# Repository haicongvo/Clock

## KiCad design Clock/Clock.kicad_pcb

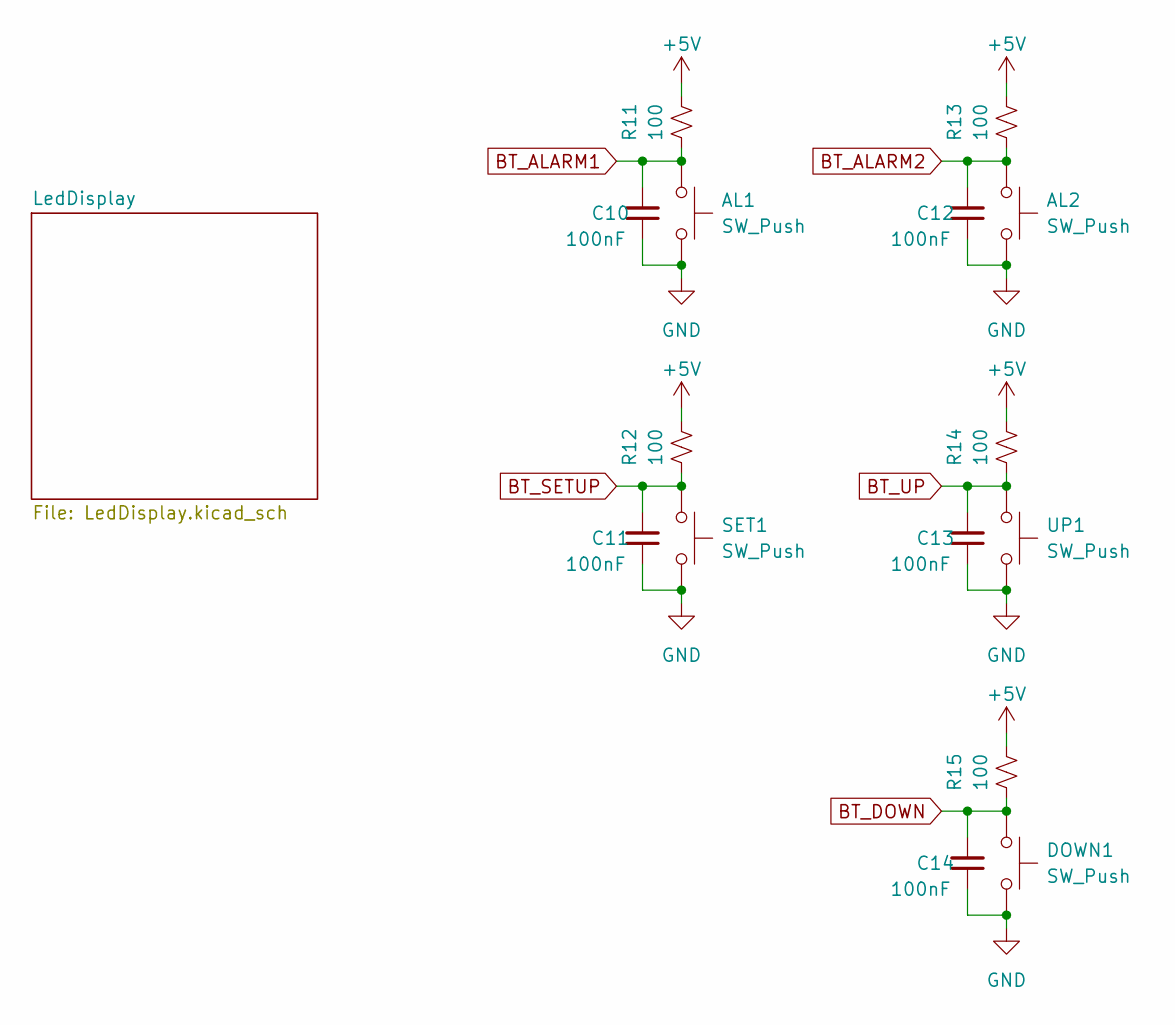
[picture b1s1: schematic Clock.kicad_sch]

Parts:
AL1, AL2: SW_Push; SW_Push_1P1T-3x6
C10, C11, C12, C13, C14: 100nF; C_0805_2012Metric_Pad1.18x1.45mm_HandSolder
DOWN1: SW_Push; SW_Push_1P1T-3x6
R11, R12, R13, R14, R15: 100; R_0805_2012Metric_Pad1.20x1.40mm_HandSolder
SET1: SW_Push; SW_Push_1P1T-3x6
UP1: SW_Push; SW_Push_1P1T-3x6

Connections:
+5V: R11.2, R12.2, R13.2, R14.2, R15.2; also elsewhere on the board
BT_ALARM1: AL1.1, C10.2, R11.1
BT_ALARM2: AL2.1, C12.2, R13.1
BT_DOWN: C14.2, DOWN1.1, R15.1
BT_SETUP: C11.2, R12.1, SET1.1
BT_UP: C13.2, R14.1, UP1.1
GND: AL1.2, AL2.2, C10.1, C11.1, C12.1, C13.1, C14.1, DOWN1.2, SET1.2, UP1.2; also elsewhere on the board

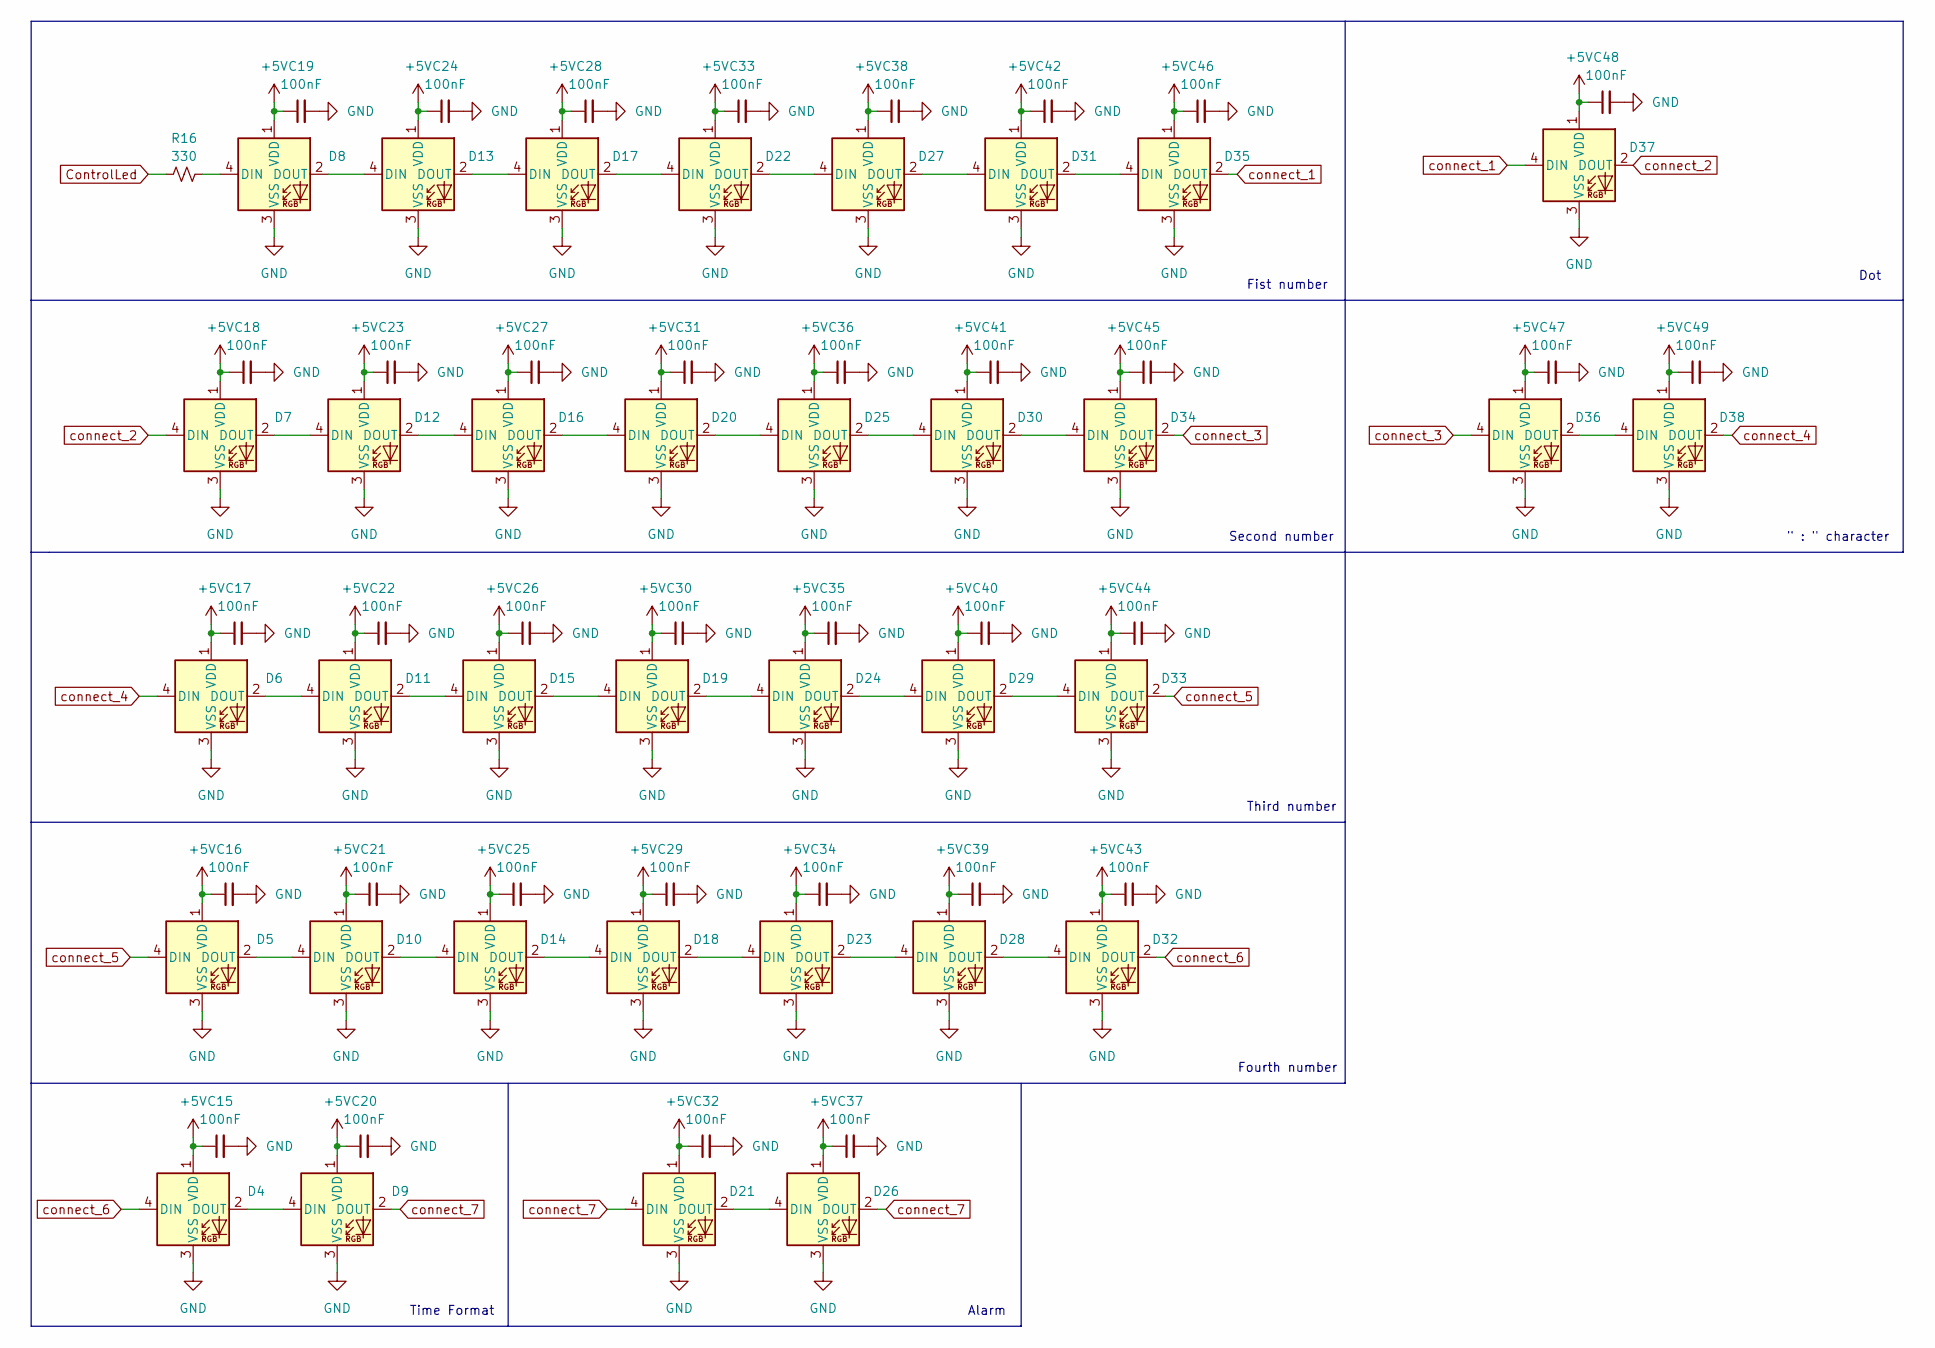
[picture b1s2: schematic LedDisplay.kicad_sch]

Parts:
C15, C16, C17, C18, C19, C20, C21, C22, C23, C24, C25, C26, C27, C28, C29, C30, C31, C32, C33, C34, C35, C36, C37, C38, C39, C40, C41, C42, C43, C44, C45, C46, C47, C48, C49: 100nF; C_0805_2012Metric_Pad1.18x1.45mm_HandSolder
D4, D5, D6, D7, D8, D9, D10, D11, D12, D13, D14, D15, D16, D17, D18, D19, D20, D21, D22, D23, D24, D25, D26, D27, D28, D29, D30, D31, D32, D33, D34, D35, D36, D37, D38: WS2812B; LED_WS2812B_PLCC4_5.0x5.0mm_P3.2mm
R16: 330; R_0805_2012Metric_Pad1.20x1.40mm_HandSolder

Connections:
+5V: C15.1, C16.1, C17.1, C18.1, C19.1, C20.1, C21.1, C22.1, C23.1, C24.1, C25.1, C26.1, C27.1, C28.1, C29.1, C30.1, C31.1, C32.1, C33.1, C34.1, C35.1, C36.1, C37.1, C38.1, C39.1, C40.1, C41.1, C42.1, C43.1, C44.1, C45.1, C46.1, C47.1, C48.1, C49.1, D4.1 (VDD), D5.1 (VDD), D6.1 (VDD), D7.1 (VDD), D8.1 (VDD), D9.1 (VDD), D10.1 (VDD), D11.1 (VDD), D12.1 (VDD), D13.1 (VDD), D14.1 (VDD), D15.1 (VDD), D16.1 (VDD), D17.1 (VDD), D18.1 (VDD), D19.1 (VDD), D20.1 (VDD), D21.1 (VDD), D22.1 (VDD), D23.1 (VDD), D24.1 (VDD), D25.1 (VDD), D26.1 (VDD), D27.1 (VDD), D28.1 (VDD), D29.1 (VDD), D30.1 (VDD), D31.1 (VDD), D32.1 (VDD), D33.1 (VDD), D34.1 (VDD), D35.1 (VDD), D36.1 (VDD), D37.1 (VDD), D38.1 (VDD); also elsewhere on the board
ControlLed: R16.1
GND: C15.2, C16.2, C17.2, C18.2, C19.2, C20.2, C21.2, C22.2, C23.2, C24.2, C25.2, C26.2, C27.2, C28.2, C29.2, C30.2, C31.2, C32.2, C33.2, C34.2, C35.2, C36.2, C37.2, C38.2, C39.2, C40.2, C41.2, C42.2, C43.2, C44.2, C45.2, C46.2, C47.2, C48.2, C49.2, D4.3 (VSS), D5.3 (VSS), D6.3 (VSS), D7.3 (VSS), D8.3 (VSS), D9.3 (VSS), D10.3 (VSS), D11.3 (VSS), D12.3 (VSS), D13.3 (VSS), D14.3 (VSS), D15.3 (VSS), D16.3 (VSS), D17.3 (VSS), D18.3 (VSS), D19.3 (VSS), D20.3 (VSS), D21.3 (VSS), D22.3 (VSS), D23.3 (VSS), D24.3 (VSS), D25.3 (VSS), D26.3 (VSS), D27.3 (VSS), D28.3 (VSS), D29.3 (VSS), D30.3 (VSS), D31.3 (VSS), D32.3 (VSS), D33.3 (VSS), D34.3 (VSS), D35.3 (VSS), D36.3 (VSS), D37.3 (VSS), D38.3 (VSS); also elsewhere on the board
unnamed: D4.2 (DOUT), D9.4 (DIN)
unnamed: D8.4 (DIN), R16.2
unnamed: D10.2 (DOUT), D14.4 (DIN)
unnamed: D5.2 (DOUT), D10.4 (DIN)
unnamed: D11.2 (DOUT), D15.4 (DIN)
unnamed: D6.2 (DOUT), D11.4 (DIN)
unnamed: D12.2 (DOUT), D16.4 (DIN)
unnamed: D7.2 (DOUT), D12.4 (DIN)
unnamed: D13.2 (DOUT), D17.4 (DIN)
unnamed: D8.2 (DOUT), D13.4 (DIN)
unnamed: D14.2 (DOUT), D18.4 (DIN)
unnamed: D15.2 (DOUT), D19.4 (DIN)
unnamed: D16.2 (DOUT), D20.4 (DIN)
unnamed: D17.2 (DOUT), D22.4 (DIN)
unnamed: D18.2 (DOUT), D23.4 (DIN)
unnamed: D19.2 (DOUT), D24.4 (DIN)
unnamed: D20.2 (DOUT), D25.4 (DIN)
unnamed: D21.2 (DOUT), D26.4 (DIN)
unnamed: D22.2 (DOUT), D27.4 (DIN)
unnamed: D23.2 (DOUT), D28.4 (DIN)
unnamed: D24.2 (DOUT), D29.4 (DIN)
unnamed: D25.2 (DOUT), D30.4 (DIN)
unnamed: D27.2 (DOUT), D31.4 (DIN)
unnamed: D28.2 (DOUT), D32.4 (DIN)
unnamed: D29.2 (DOUT), D33.4 (DIN)
unnamed: D30.2 (DOUT), D34.4 (DIN)
unnamed: D31.2 (DOUT), D35.4 (DIN)
unnamed: D36.2 (DOUT), D38.4 (DIN)
connect_1: D35.2 (DOUT), D37.4 (DIN)
connect_2: D7.4 (DIN), D37.2 (DOUT)
connect_3: D34.2 (DOUT), D36.4 (DIN)
connect_4: D6.4 (DIN), D38.2 (DOUT)
connect_5: D5.4 (DIN), D33.2 (DOUT)
connect_6: D4.4 (DIN), D32.2 (DOUT)
connect_7: D9.2 (DOUT), D21.4 (DIN), D26.2 (DOUT)

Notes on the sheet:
Fourth number
Time Format
" : " character
Alarm
Fist number
Second number
Dot
Third number

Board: 2 copper layers, 88 parts (0 on the bottom side), 42 nets, no tracks yet.

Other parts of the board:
R3, R4: 10K; R_0805_2012Metric_Pad1.20x1.40mm_HandSolder

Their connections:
+5V: R3.2, R4.2; also elsewhere on the board

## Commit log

2023-01-05 update schematic
2023-01-09 update PCB 09/1/2022
